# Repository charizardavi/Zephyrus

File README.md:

# Zephyrus: A VTOL
## Phillips Exeter Academy Senior Project, Fall 2025

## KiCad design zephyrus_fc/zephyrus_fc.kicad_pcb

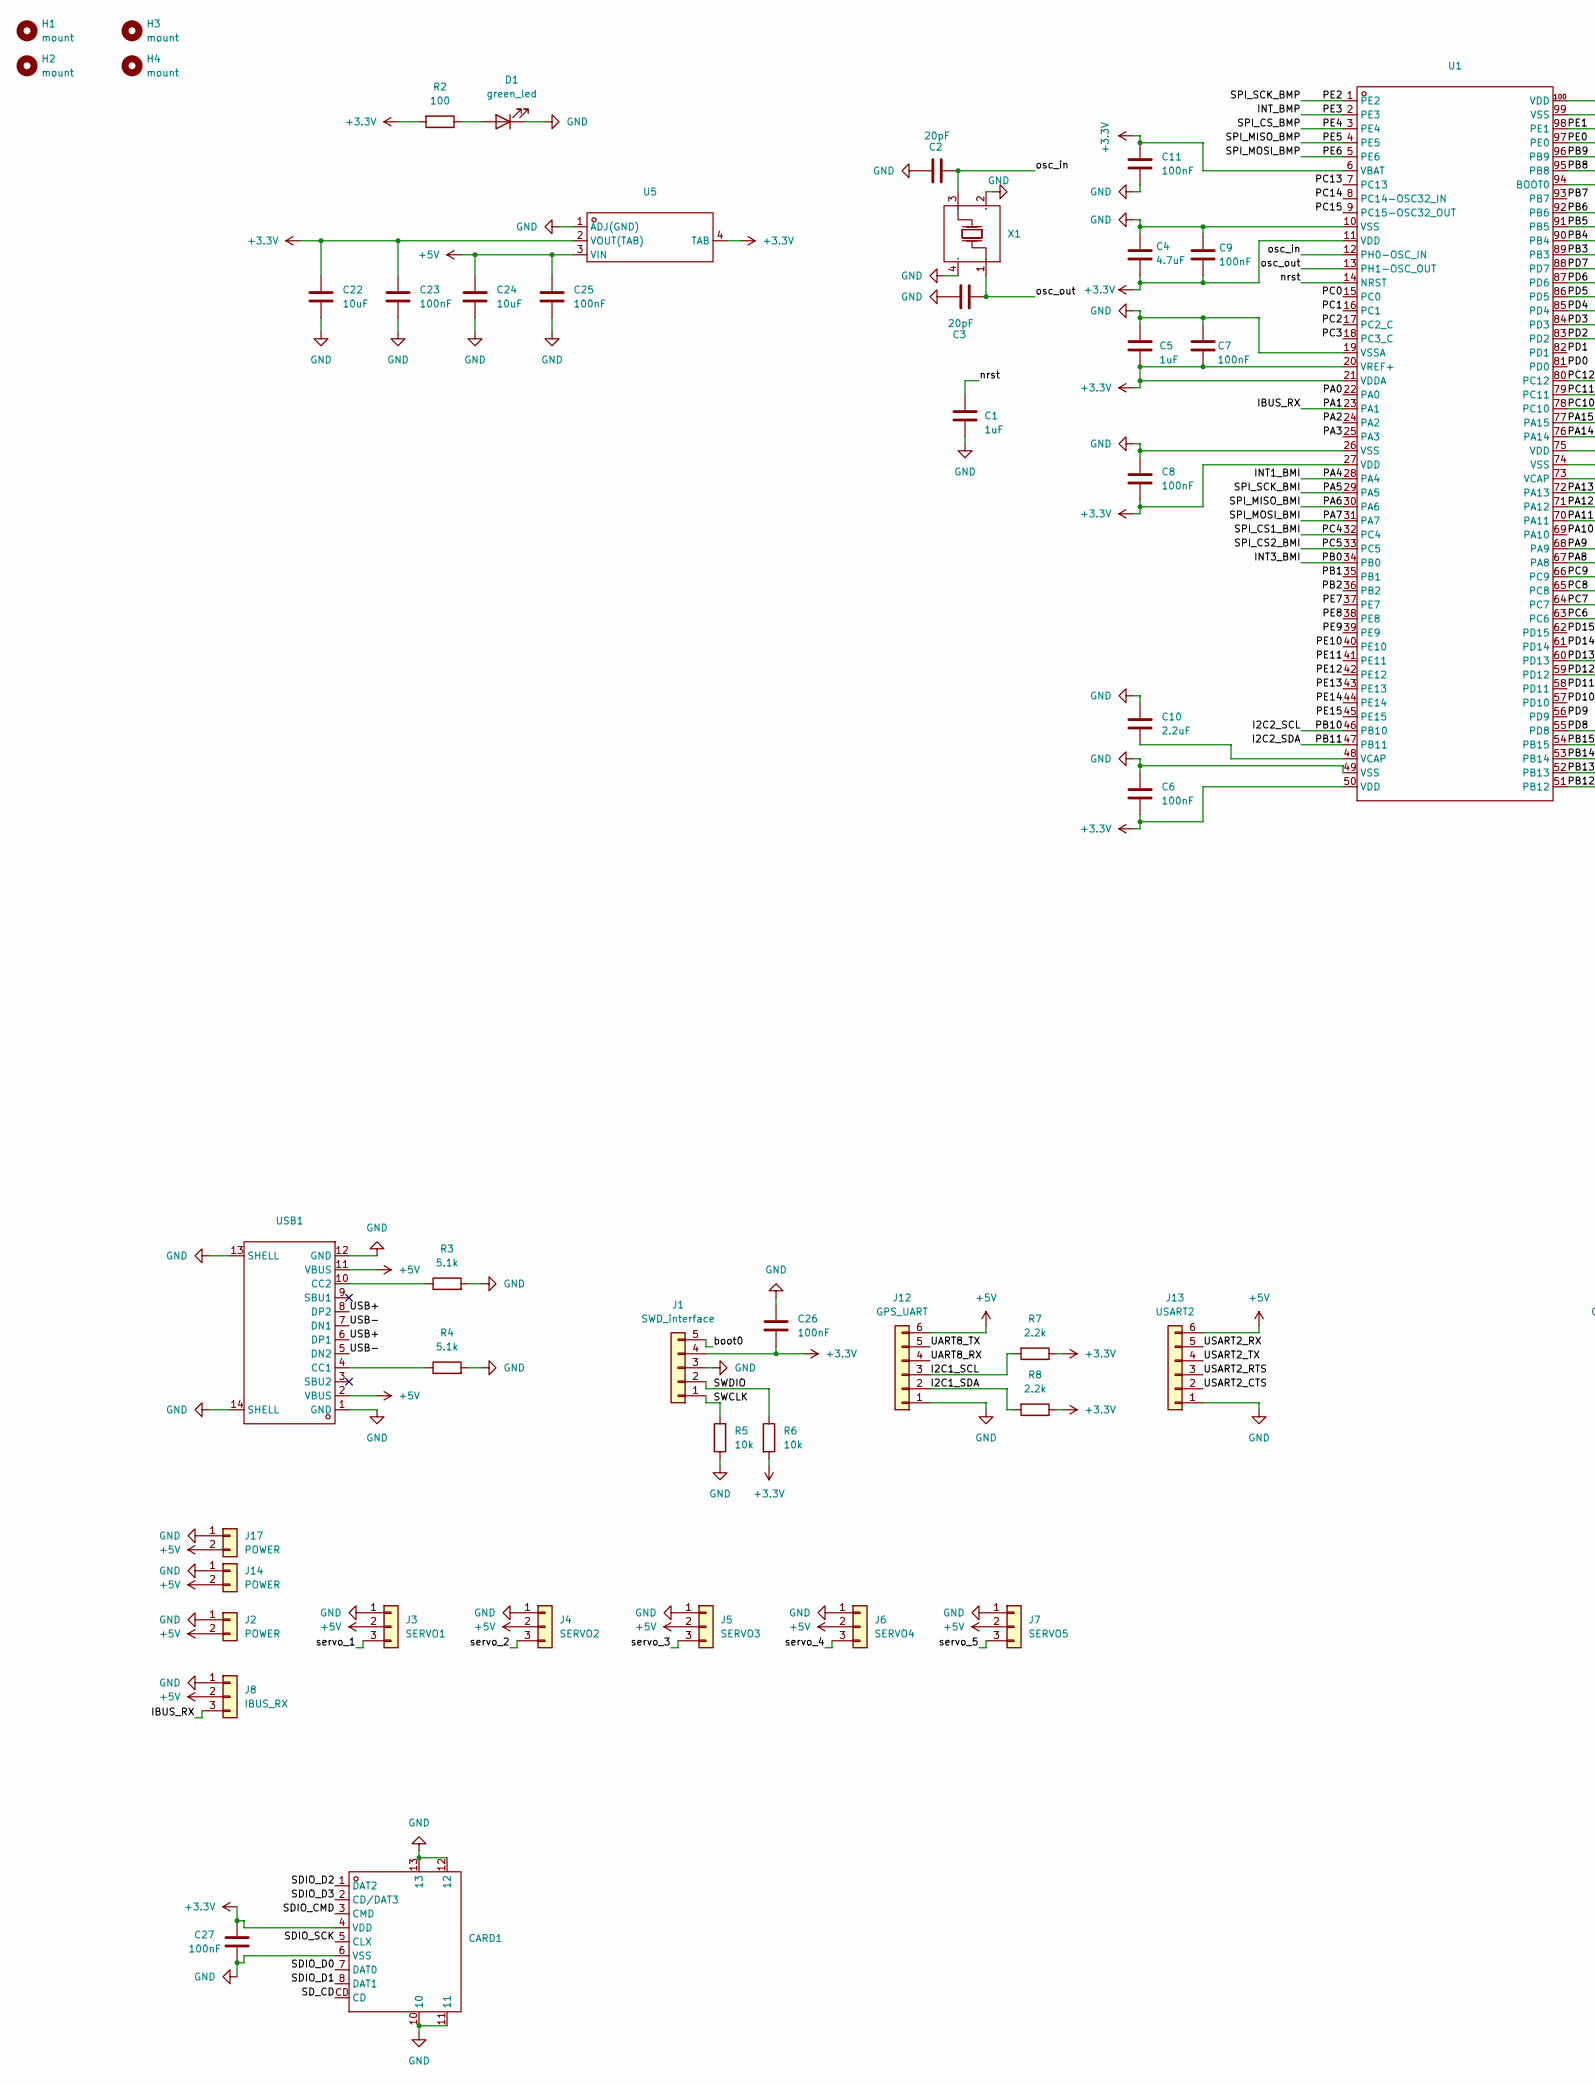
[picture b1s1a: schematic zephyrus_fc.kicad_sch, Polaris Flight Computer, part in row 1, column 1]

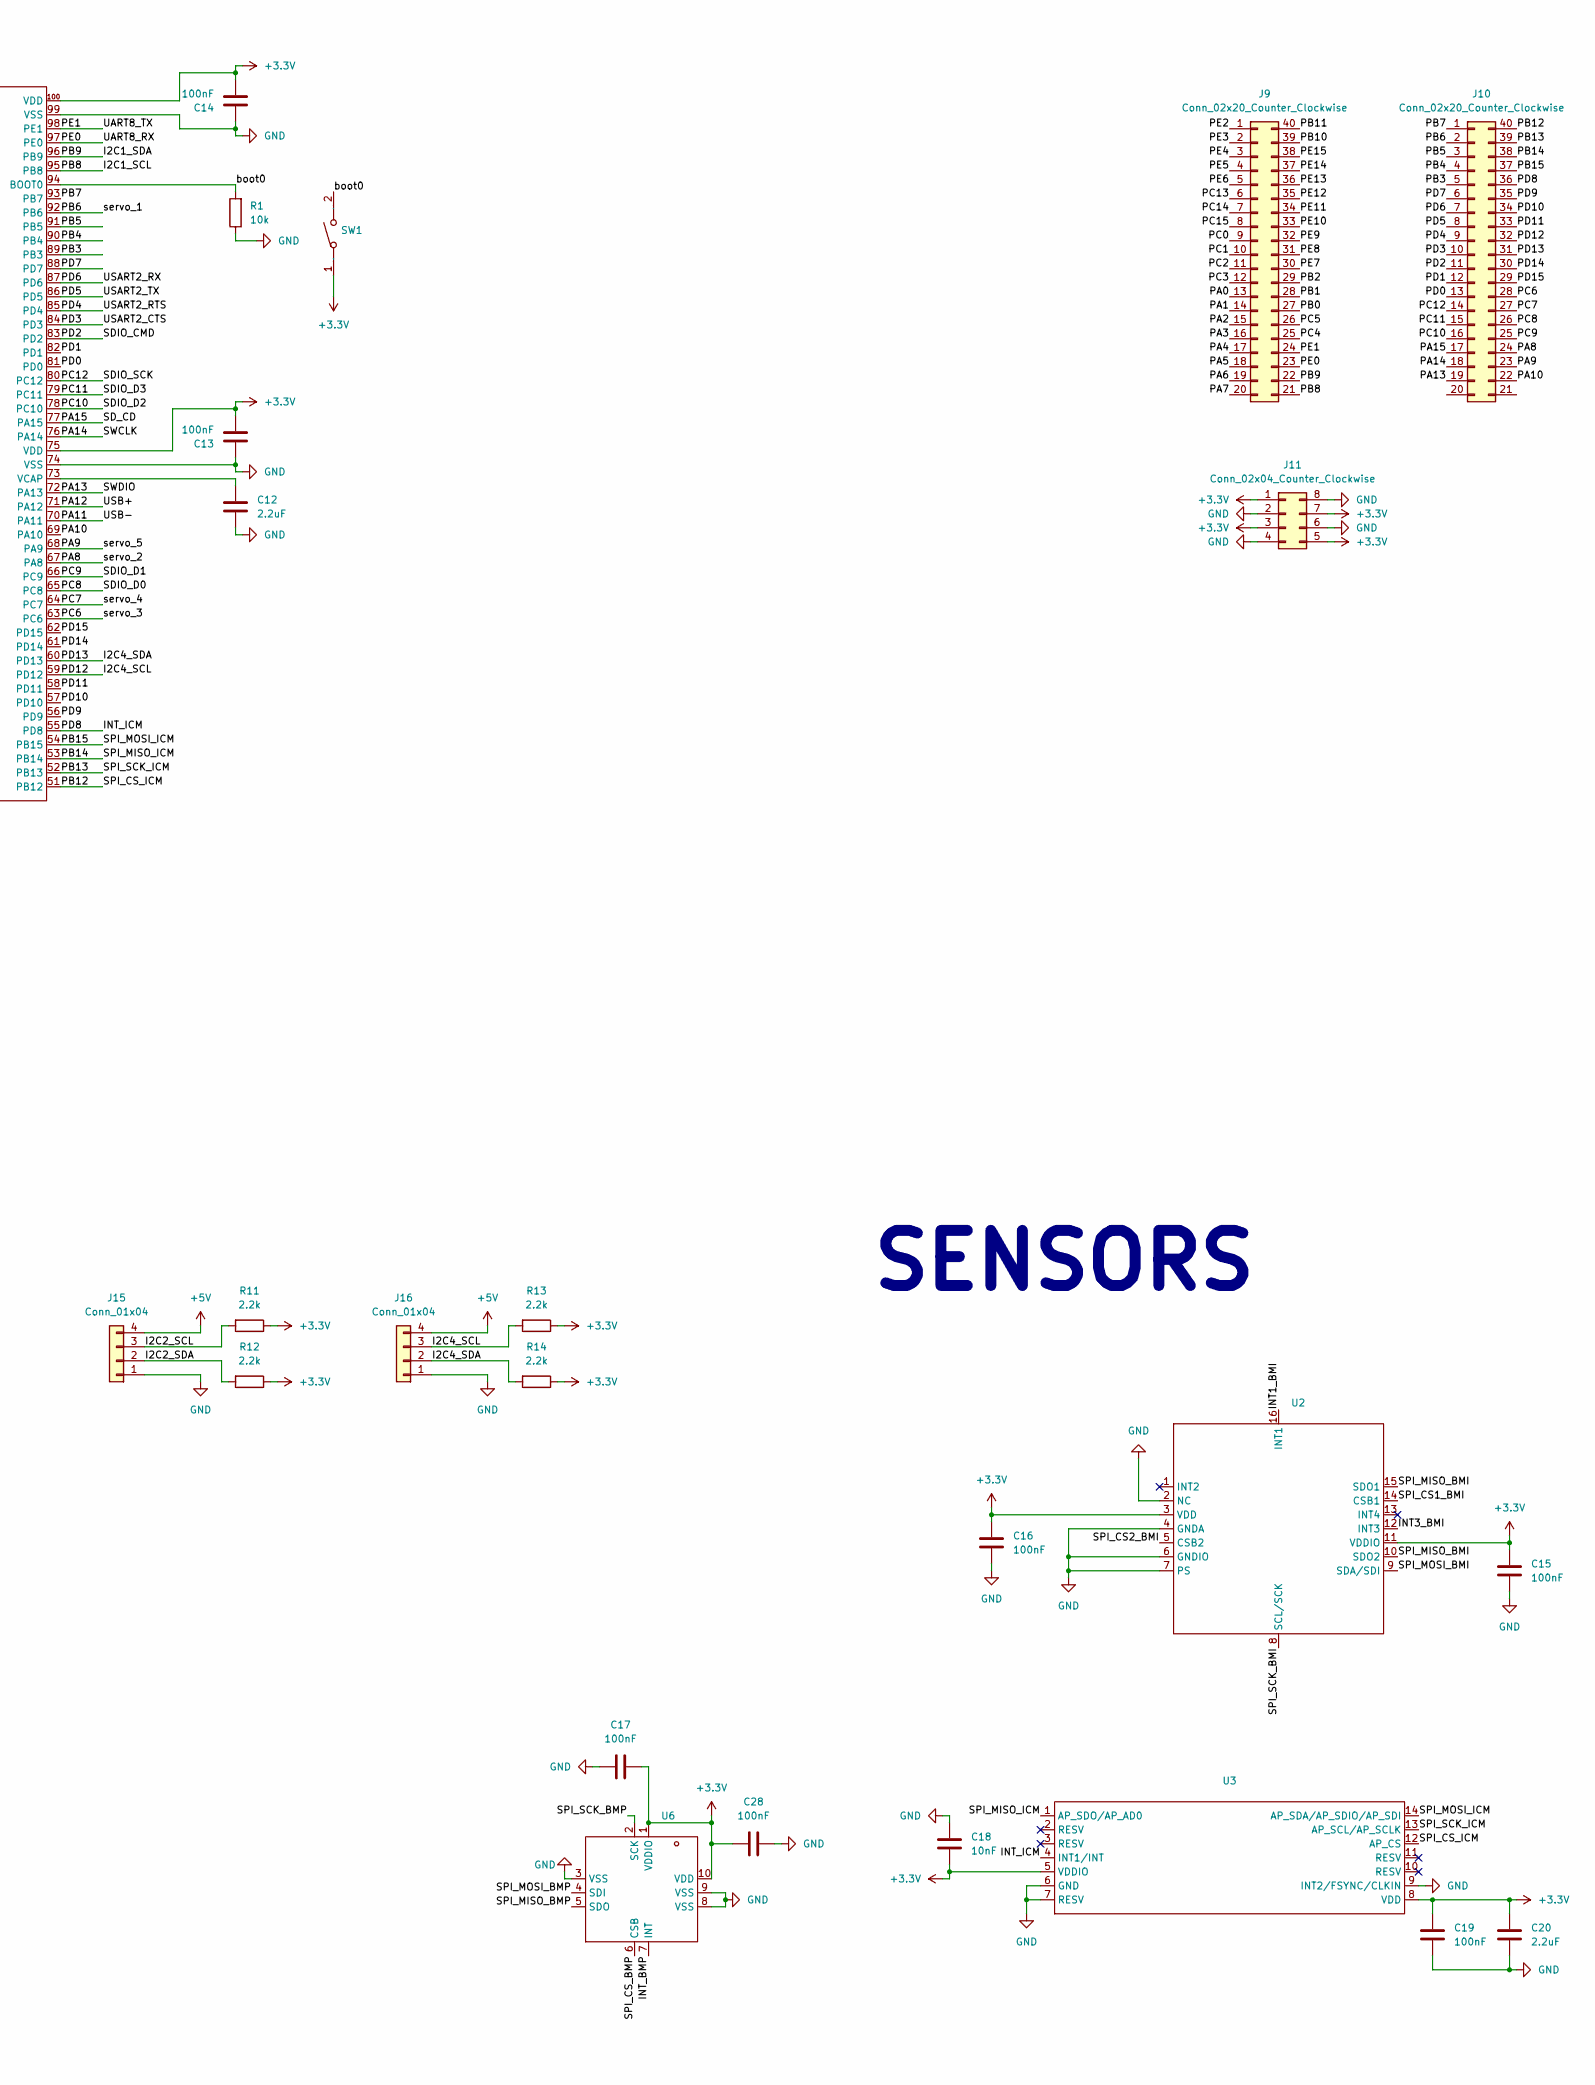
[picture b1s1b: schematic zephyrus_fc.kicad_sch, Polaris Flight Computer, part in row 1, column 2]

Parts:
C1, C5: 1uF; C_0402_1005Metric
C2, C3: 20pF; C_0402_1005Metric
C4: 4.7uF; C_0402_1005Metric
C6, C7, C8, C9, C11, C13, C14, C15, C16, C17, C19, C23, C25, C26, C27, C28: 100nF; C_0402_1005Metric
C10, C12, C20: 2.2uF; C_0402_1005Metric
C18: 10nF; C_0402_1005Metric
C22, C24: 10uF; C_0402_1005Metric
CARD1: TF-SMD_TF-PUSH; Manufacturer Part TF PUSH; LCSC Part Name 自弹式 MicroSD卡(TF卡) 卡座
D1: green_led; LED_0603_1608Metric
H1, H2, H3, H4: mount; MountingHole_3.2mm_M3
J1: SWD_interface; PinHeader_1x05_P2.54mm_Vertical
J2, J14, J17: POWER; PinHeader_1x02_P2.54mm_Vertical
J3: SERVO1; PinHeader_1x03_P2.54mm_Vertical
J4: SERVO2; PinHeader_1x03_P2.54mm_Vertical
J5: SERVO3; PinHeader_1x03_P2.54mm_Vertical
J6: SERVO4; PinHeader_1x03_P2.54mm_Vertical
J7: SERVO5; PinHeader_1x03_P2.54mm_Vertical
J8: IBUS_RX; PinHeader_1x03_P2.54mm_Vertical
J9, J10: Conn_02x20_Counter_Clockwise; PinHeader_2x20_P2.54mm_Vertical
J11: Conn_02x04_Counter_Clockwise; PinHeader_2x04_P2.54mm_Vertical
J12: GPS_UART; PinHeader_1x06_P2.54mm_Vertical
J13: USART2; PinHeader_1x06_P2.54mm_Vertical
J15, J16: Conn_01x04; PinHeader_1x04_P2.54mm_Vertical
R1, R5, R6: 10k; R_0402_1005Metric
R2: 100; R_0402_1005Metric
R3, R4: 5.1k; R_0402_1005Metric
R7, R8, R11, R12, R13, R14: 2.2k; R_0402_1005Metric
SW1: SW-SMD_L3.9-W3.0-P4.45; Manufacturer Part TS-1088-AR02016; LCSC Part Name 4*3*2mm 立贴 轻触开关
U1: QFP-100_L14.0-W14.0-P0.50-LS16.0-BL; Manufacturer Part STM32H750VBT6TR; LCSC Part Name 带DSP和DP-FPU的高性能ARM Cortex-M7 MCU，具有128 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
U2: LGA-16_L4.5-W3.0-P0.50-BL; Manufacturer Part BMI088; LCSC Part Name BMI088
U3: LGA-14_L3.0-W2.5-P0.50-TL; Manufacturer Part ICM-42688-P; LCSC Part Name ICM-42688-P
U5: SOT-223-4_L6.5-W3.5-P2.30-LS7.0-BR; Manufacturer Part AMS1117-3.3; LCSC Part Name 输出:3.3V 电流:1A 耐压:12V
U6: SENSORM-SMD_BMP388; Manufacturer Part BMP388; LCSC Part Name BMP388
USB1: USB-C-SMD_TYPE-C-6PIN-2MD-073; Manufacturer Part TYPE-C 16PIN 2MD(073); LCSC Part Name Type-C 母 卧贴
X1: 25MHz; OSC-SMD_4P-L3.2-W2.5-BL; Manufacturer Part X322525MSB4SI; LCSC Part Name 25MHz ±10ppm 20pF

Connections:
+3.3V: C4.2, C5.1, C6.1, C7.1, C8.1, C9.1, C11.1, C13.1, C14.1, C15.2, C16.2, C17.1, C18.1, C19.2, C20.2, C22.1, C23.1, C26.1, C27.2, C28.1, CARD1.4 (VDD), J1.4, J11.1, J11.3, J11.5, J11.7, R2.2, R6.2, R7.1, R8.1, R11.1, R12.1, R13.1, R14.1, SW1.1, U1.6 (VBAT), U1.11 (VDD), U1.20 (VREF+), U1.21 (VDDA), U1.27 (VDD), U1.50 (VDD), U1.75 (VDD), U1.100 (VDD), U2.3 (VDD), U2.11 (VDDIO), U3.5 (VDDIO), U3.8 (VDD), U5.2 (VOUT(TAB)), U5.4 (TAB), U6.1 (VDDIO), U6.10 (VDD)
+5V: C24.1, C25.1, J2.2, J3.2, J4.2, J5.2, J6.2, J7.2, J8.2, J12.6, J13.6, J14.2, J15.4, J16.4, J17.2, U5.3 (VIN), USB1.2 (VBUS), USB1.11 (VBUS)
/I2C1_SCL: J9.21, J12.3, R7.2, U1.95 (PB8)
/I2C1_SDA: J9.22, J12.2, R8.2, U1.96 (PB9)
/I2C2_SCL: J9.39, J15.3, R11.2, U1.46 (PB10)
/I2C2_SDA: J9.40, J15.2, R12.2, U1.47 (PB11)
/I2C4_SCL: J10.32, J16.3, R13.2, U1.59 (PD12)
/I2C4_SDA: J10.31, J16.2, R14.2, U1.60 (PD13)
/IBUS_RX: J8.3, J9.14, U1.23 (PA1)
/INT1_BMI: J9.17, U1.28 (PA4), U2.16 (INT1)
/INT3_BMI: J9.27, U1.34 (PB0), U2.12 (INT3)
/INT_BMP: J9.2, U1.2 (PE3), U6.7 (INT)
/INT_ICM: J10.36, U1.55 (PD8), U3.4 (INT1/INT)
/PA0: J9.13, U1.22 (PA0)
/PA2: J9.15, U1.24 (PA2)
/PA3: J9.16, U1.25 (PA3)
/PA5: J9.18, U1.29 (PA5), U2.8 (SCL/SCK)
/PA6: J9.19, U1.30 (PA6), U2.10 (SDO2), U2.15 (SDO1)
/PA7: J9.20, U1.31 (PA7), U2.9 (SDA/SDI)
/PA8: J4.3, J10.24, U1.67 (PA8)
/PA9: J7.3, J10.23, U1.68 (PA9)
/PA10: J10.22, U1.69 (PA10)
/PA11: U1.70 (PA11), USB1.5 (DN2), USB1.7 (DN1)
/PA12: U1.71 (PA12), USB1.6 (DP1), USB1.8 (DP2)
/PA13: J1.2, J10.19, R6.1, U1.72 (PA13)
/PA14: J1.1, J10.18, R5.2, U1.76 (PA14)
/PA15: CARD1.CD, J10.17, U1.77 (PA15)
/PB1: J9.28, U1.35 (PB1)
/PB2: J9.29, U1.36 (PB2)
/PB3: J10.5, U1.89 (PB3)
/PB4: J10.4, U1.90 (PB4)
/PB5: J10.3, U1.91 (PB5)
/PB6: J3.3, J10.2, U1.92 (PB6)
/PB7: J10.1, U1.93 (PB7)
/PB12: J10.40, U1.51 (PB12), U3.12 (AP_CS)
/PB13: J10.39, U1.52 (PB13), U3.13 (AP_SCL/AP_SCLK)
/PB14: J10.38, U1.53 (PB14), U3.1 (AP_SDO/AP_AD0)
/PB15: J10.37, U1.54 (PB15), U3.14 (AP_SDA/AP_SDIO/AP_SDI)
/PC0: J9.9, U1.15 (PC0)
/PC1: J9.10, U1.16 (PC1)
/PC2: J9.11, U1.17 (PC2_C)
/PC3: J9.12, U1.18 (PC3_C)
/PC4: J9.25, U1.32 (PC4), U2.14 (CSB1)
/PC5: J9.26, U1.33 (PC5), U2.5 (CSB2)
/PC6: J5.3, J10.28, U1.63 (PC6)
/PC7: J6.3, J10.27, U1.64 (PC7)
/PC8: CARD1.7 (DAT0), J10.26, U1.65 (PC8)
/PC9: CARD1.8 (DAT1), J10.25, U1.66 (PC9)
/PC10: CARD1.1 (DAT2), J10.16, U1.78 (PC10)
/PC11: CARD1.2 (CD/DAT3), J10.15, U1.79 (PC11)
/PC12: CARD1.5 (CLX), J10.14, U1.80 (PC12)
/PC13: J9.6, U1.7 (PC13)
/PC14: J9.7, U1.8 (PC14-OSC32_IN)
/PC15: J9.8, U1.9 (PC15-OSC32_OUT)
/PD0: J10.13, U1.81 (PD0)
/PD1: J10.12, U1.82 (PD1)
/PD2: CARD1.3 (CMD), J10.11, U1.83 (PD2)
/PD3: J10.10, J13.2, U1.84 (PD3)
/PD4: J10.9, J13.3, U1.85 (PD4)
/PD5: J10.8, J13.4, U1.86 (PD5)
/PD6: J10.7, J13.5, U1.87 (PD6)
/PD7: J10.6, U1.88 (PD7)
/PD9: J10.35, U1.56 (PD9)
/PD10: J10.34, U1.57 (PD10)
/PD11: J10.33, U1.58 (PD11)
/PD14: J10.30, U1.61 (PD14)
/PD15: J10.29, U1.62 (PD15)
/PE0: J9.23, J12.4, U1.97 (PE0)
/PE1: J9.24, J12.5, U1.98 (PE1)
/PE2: J9.1, U1.1 (PE2), U6.2 (SCK)
/PE4: J9.3, U1.3 (PE4), U6.6 (CSB)
/PE5: J9.4, U1.4 (PE5), U6.5 (SDO)
/PE6: J9.5, U1.5 (PE6), U6.4 (SDI)
/PE7: J9.30, U1.37 (PE7)
/PE8: J9.31, U1.38 (PE8)
/PE9: J9.32, U1.39 (PE9)
/PE10: J9.33, U1.40 (PE10)
/PE11: J9.34, U1.41 (PE11)
/PE12: J9.35, U1.42 (PE12)
/PE13: J9.36, U1.43 (PE13)
/PE14: J9.37, U1.44 (PE14)
/PE15: J9.38, U1.45 (PE15)
/boot0: J1.5, R1.2, SW1.2, U1.94 (BOOT0)
/nrst: C1.2, U1.14 (NRST)
/osc_in: C2.1, U1.12 (PH0-OSC_IN), X1.3 (OSC2)
/osc_out: C3.1, U1.13 (PH1-OSC_OUT), X1.1 (OSC1)
GND: C1.1, C2.2, C3.2, C4.1, C5.2, C6.2, C7.2, C8.2, C9.2, C10.2, C11.2, C12.2, C13.2, C14.2, C15.1, C16.1, C17.2, C18.2, C19.1, C20.1, C22.2, C23.2, C24.2, C25.2, C26.2, C27.1, C28.2, CARD1.6 (VSS), CARD1.10, CARD1.11, CARD1.12, CARD1.13, D1.1 (K), J1.3, J2.1, J3.1, J4.1, J5.1, J6.1, J7.1, J8.1, J11.2, J11.4, J11.6, J11.8, J12.1, J13.1, J14.1, J15.1, J16.1, J17.1, R1.1, R3.2, R4.2, R5.1, U1.10 (VSS), U1.19 (VSSA), U1.26 (VSS), U1.49 (VSS), U1.74 (VSS), U1.99 (VSS), U2.2 (NC), U2.4 (GNDA), U2.6 (GNDIO), U2.7 (PS), U3.6 (GND), U3.7 (RESV), U3.9 (INT2/FSYNC/CLKIN), U5.1 (ADJ(GND)), U6.3 (VSS), U6.8 (VSS), U6.9 (VSS), USB1.1 (GND), USB1.12 (GND), USB1.13 (SHELL), USB1.14 (SHELL), X1.2 (GND), X1.4 (GND)
unnamed: C10.1, U1.48 (VCAP)
unnamed: C12.1, U1.73 (VCAP)
unnamed: D1.2 (A), R2.1
unnamed: R4.1, USB1.4 (CC1)
unnamed: R3.1, USB1.10 (CC2)

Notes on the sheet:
SENSORS

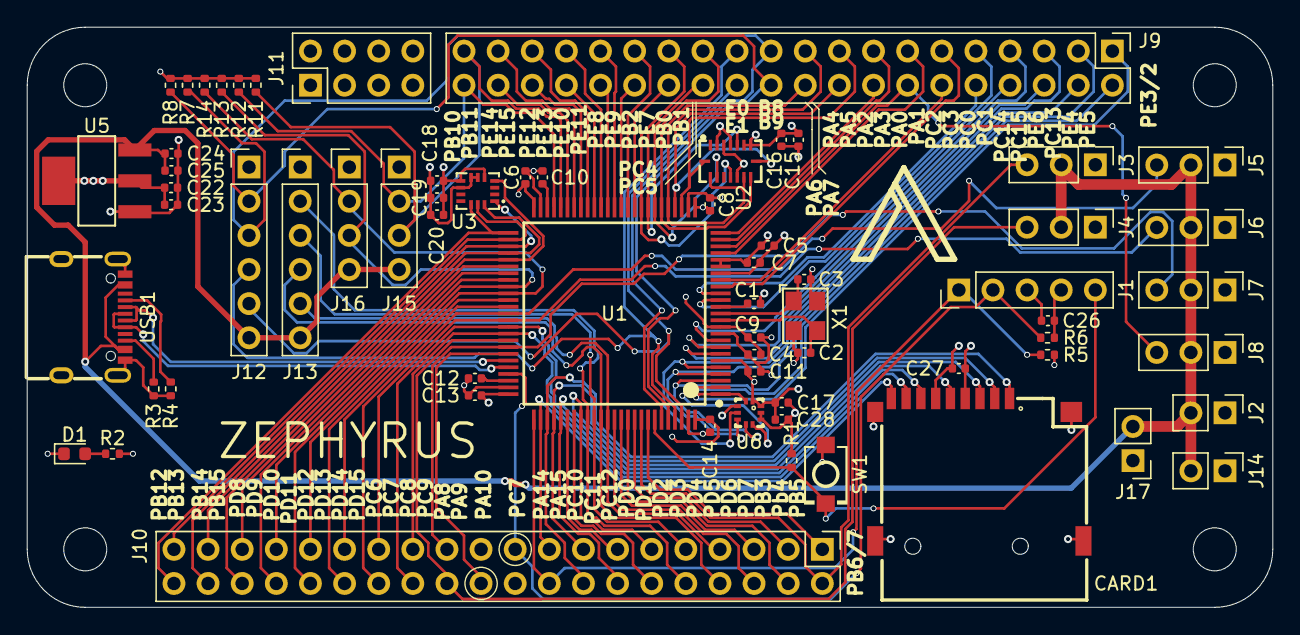
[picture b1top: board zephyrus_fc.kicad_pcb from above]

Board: 4 copper layers, 92.7 x 43.2 mm, 70 parts (0 on the bottom side), 92 nets.

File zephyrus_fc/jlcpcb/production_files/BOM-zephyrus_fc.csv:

Comment,Designator,Footprint,LCSC
20pF,"C2,C3",C_0402_1005Metric,C107000
~,U1,QFP-100_L14.0-W14.0-P0.50-LS16.0-BL,C114409
2.2k,"R11,R12,R13,R14,R7,R8",R_0402_1005Metric,C114762
25MHz,X1,OSC-SMD_4P-L3.2-W2.5-BL,C13740
1uF,"C1,C5",C_0402_1005Metric,C14445
2.2uF,"C10,C12,C20",C_0402_1005Metric,C170151
~,U3,LGA-14_L3.0-W2.5-P0.50-TL,C1850418
~,U2,LGA-16_L4.5-W3.0-P0.50-BL,C194919
100,R2,R_0402_1005Metric,C25076
10k,"R1,R5,R6",R_0402_1005Metric,C25744
5.1k,"R3,R4",R_0402_1005Metric,C25905
~,USB1,USB-C-SMD_TYPE-C-6PIN-2MD-073,C2765186
~,U5,SOT-223-4_L6.5-W3.5-P2.30-LS7.0-BR,C347222
4.7uF,C4,C_0402_1005Metric,C368809
~,CARD1,TF-SMD_TF-PUSH,C393941
10nF,C18,C_0402_1005Metric,C60133
100nF,"C11,C13,C14,C15,C16,C17,C19,C23,C25,C26,C27,C28,C6,C7,C8,C9",C_0402_1005Metric,C60474
~,SW1,SW-SMD_L3.9-W3.0-P4.45,C720477
10uF,"C22,C24",C_0402_1005Metric,C77000
~,U6,SENSORM-SMD_BMP388,C779278
green_led,D1,LED_0603_1608Metric,C965799

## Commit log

2025-08-22 PCB mostly done
2025-08-23 ready to order
2025-08-25 silkscreened
